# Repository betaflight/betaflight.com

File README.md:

## Project Description

This platform serves as a central hub for everything related to Betaflight, a popular open-source flight controller software used in FPV (First Person View) drones. This project provides users with documentation, development guidelines, downloads, build statistics, relations with sponsors, and blog updates. The website was built using [Docusaurus 2](https://docusaurus.io/), a modern static website generator. Our goal is to offer a user-friendly platform where users can easily access accurate and helpful resources, contributing to the overall improvement of the Betaflight community.

## Table of Contents

1. [Installation and Setup](#installation-and-setup)
2. [Usage Instructions](#usage-instructions)
3. [Troubleshooting](#troubleshooting)
4. [Build](#build)
5. [Deployment](#deployment)
6. [ESLint Prettier](#eslint-prettier)
7. [Contributing Guidelines](#contributing-guidelines)

## Installation and Setup

This project primarily consists of a documentation website built using Docusaurus. To run the project locally, follow these steps on a Linux machine:

Fork the repository. Then, clone the forked GitHub repository to your local machine:

```bash
git clone https://github.com/<yourusername>/betaflight.com.git
```

Navigate to the project directory:

```bash
cd betaflight.com
```

Install dependencies using npm:

```bash
npm i
```

If npm is not installed and you are using Linux, you can typically install npm using your distribution's package manager. For example, on Debian or Ubuntu-based systems, you can use apt:

```bash
sudo apt update
sudo apt install npm
```

Copy the .env.example file to .env and configure it according to your setup.

```bash
cp .env.example .env
```

The default is for a standard development environment:

```bash
URL=http://localhost:3000
BASE_PATH=/
ORG=betaflight
```

## Start the Local Development server

```bash
npm start
```

This command starts a local development server and opens up a browser window at http://localhost:3000. Most changes are reflected live without having to restart the server.

## Usage Instructions

Once Betaflight is set up, you can access the website locally through your browser. Users can easily navigate through the various sections of the platform to find the information they need. The Wiki section provides detailed documentation on Betaflight-related topics. The Development section is primarily for developers on how to contribute. The Downloads section offers access to essential resources such as Betaflight App, Firmware, Lua Tx Scripts, BlackBox Log Viewer, and more. Additionally, users can check Build Statistics, find Betaflight Sponsors, and stay up-to-date with the latest developments and announcements by checking the Blog section.

## Troubleshooting

If you encounter an issue while running npm start, especially related to syntax errors, it might be due to an incompatible version of Node.js. Follow these steps to resolve the issue:

Remove the current version of Node.js:

```bash
sudo apt remove nodejs
```

Install nvm (Node Version Manager) if you haven't already:

```bash
curl -o- https://raw.githubusercontent.com/nvm-sh/nvm/v0.39.1/install.sh | bash
```

Close and reopen your terminal to start using nvm, or run:

```bash
source ~/.bashrc
```

Install the latest LTS version of Node.js:

```bash
nvm install --lts
```

Activate the LTS version:

```bash
nvm use --lts
```

Try starting the application again by running:

```bash
npm run
```

## Build

To build the website for deployment, use the following command:

```bash
npm run build
```

This command generates static content into the `build` directory and can be served using any static contents hosting service.

## Deployment

Using SSH:

```bash
USE_SSH=true npm run deploy
```

Not using SSH:

```bash
GIT_USER=<Your GitHub username> npm run deploy
```

If you are using GitHub pages for hosting, this command is a convenient way to build the website and push to the `gh-pages` branch.

## ESLint Prettier

We use eslint and prettier for code formatting.

Husky is configured as a pre-commit hook to run both on commit, make sure it is setup correct and it runns before you commit your code.

## Contributing Guidelines

Please refer to the [CONTRIBUTING.md](./CONTRIBUTION.md) file for detailed guidelines on how to contribute to Betaflight.

Contributors agree to the [Contributor Licence Agreement](./CLA.md) when they open a pull request. See [LICENSE.md](./LICENSE.md) for the licence of the site and its content.

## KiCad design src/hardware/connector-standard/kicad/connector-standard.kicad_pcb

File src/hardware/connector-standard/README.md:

# Connector Standard Render Source

The KiCad project in `kicad/` is the source for the connector-standard schematic and PCB images published from `static/img/connector_standard/`.

## Crop Areas

Each connector must have the same lowercase, hyphenated crop name in both editors, for example `esc-connector`.

In the Schematic Editor:

1. Draw one rectangular rule area around the connector.
2. Leave all rule-area attributes disabled.
3. Group the rule area with the connector circuit.
4. Give the group the crop name.

In the PCB Editor:

1. Draw one rectangular rule area around the board coupon.
2. Allow tracks, vias, pads, copper pours, and footprints, and disable placement rules.
3. Give the rule area the same crop name as the schematic group.

The renderer validates that crop areas are axis-aligned rectangles, names are unique, and the two editors contain the same names. Hyphens in crop names become underscores in generated filenames.

Schematic crop guides are removed from a temporary project copy before export. PCB rule areas do not appear in the 3D renderer. The checked-in KiCad project is never modified by the script.

The PCB render uses the solder-mask colors from **Board Setup → Board Stackup → Physical Stackup**. Set both mask layers to black there to match the current connector-standard artwork.

## Commands

Install Node.js 20 or later and KiCad 10.0.0, then run:

```sh
npm ci
npm run validate:connector-standard
npm run render:connector-standard
```

`render:connector-standard` locates `kicad-cli` on `PATH` and in the standard KiCad 10 Windows installation directory. Set `KICAD_CLI` to use another executable:

```sh
KICAD_CLI=/opt/kicad/bin/kicad-cli npm run render:connector-standard
```

Generated files retain the existing documentation filenames:

```text
static/img/connector_standard/esc_connector_schematic.png
static/img/connector_standard/esc_connector_render.png
static/img/connector_standard/uart_connector_schematic.png
static/img/connector_standard/uart_connector_render.png
static/img/connector_standard/bf_connector_standard.svg
static/img/connector_standard/bf_connector_standard.pdf
```

CI runs `npm run check:connector-standard`, which renders into a temporary directory and fails when the generated artwork differs from its committed counterpart. PNG and SVG comparisons allow only a tightly bounded one-level antialiasing difference between platforms. The PDF embeds a deterministic SHA-256 source fingerprint and is checked by that fingerprint and its stable document structure because KiCad orders visually equivalent PDF drawing streams differently on Windows and Linux.

The repository-owned `render-theme.json` controls schematic colors, default PCB materials, lighting background, and other presentation details. Explicit board-stackup colors take precedence over its material defaults. KiCad is given an isolated temporary configuration directory, so rendering does not modify or depend on the user's KiCad preferences.

Geist Bold and Geist Mono Medium 1.7.2 are vendored in `fonts/` under the SIL Open Font License. The renderer exposes only this repository-owned font directory to KiCad, uses Geist Mono Medium for the schematic SVG and cropped schematic images, and uses Geist Bold for PCB silkscreen text. The downloadable schematic PDF retains KiCad's built-in stroke font because KiCad writes outline-font PDF subsets in nondeterministic order.

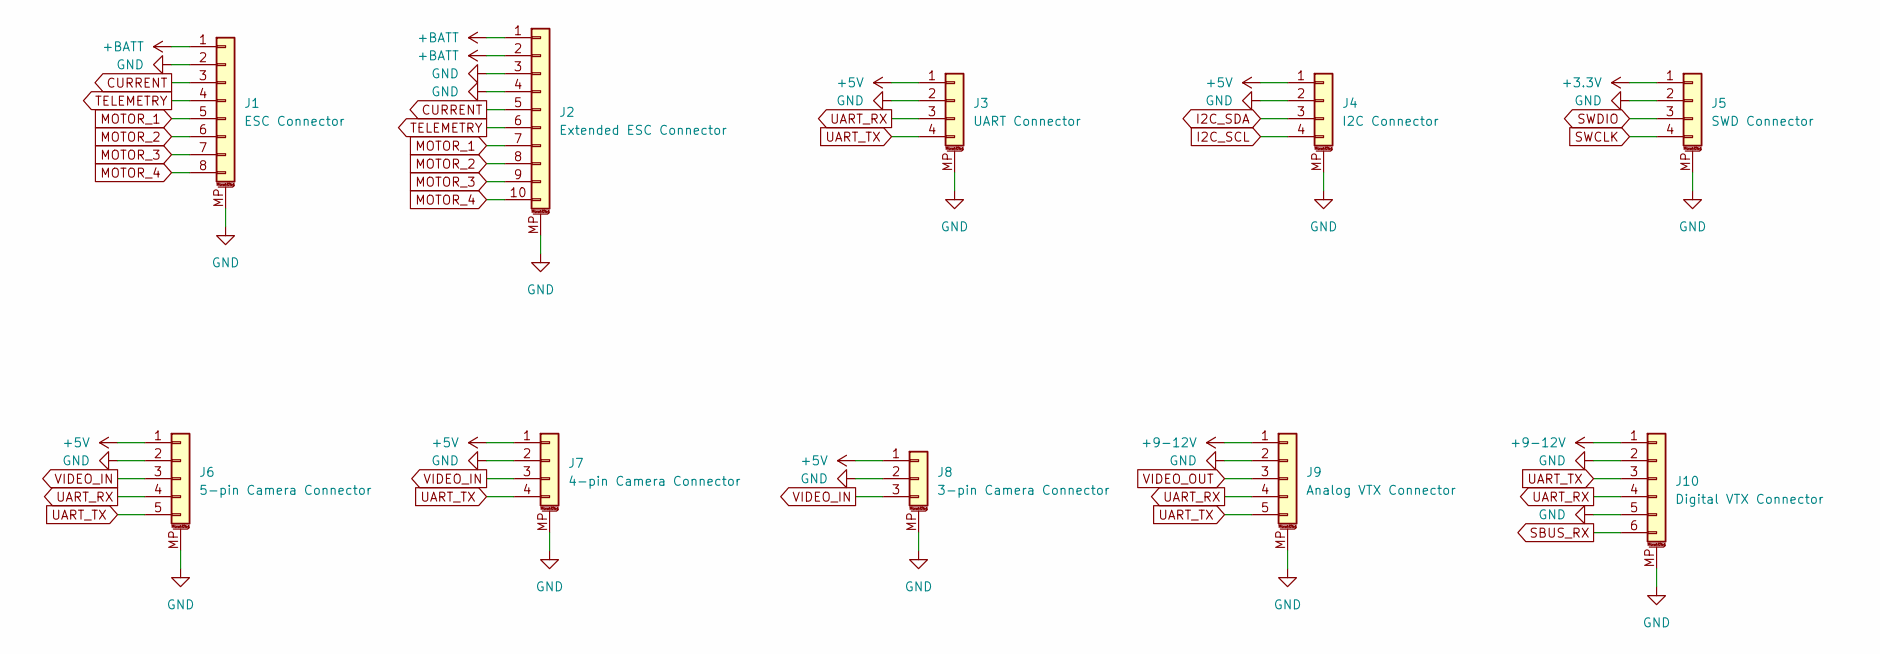
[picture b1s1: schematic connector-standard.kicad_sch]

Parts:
J1: ESC Connector; JST_SH_SM08B-SRSS-TB_1x08-1MP_P1.00mm_Horizontal
J2: Extended ESC Connector; JST_SH_SM10B-SRSS-TB_1x10-1MP_P1.00mm_Horizontal
J3: UART Connector; JST_SH_SM04B-SRSS-TB_1x04-1MP_P1.00mm_Horizontal
J4: I2C Connector; JST_SH_SM04B-SRSS-TB_1x04-1MP_P1.00mm_Horizontal
J5: SWD Connector; JST_SH_SM04B-SRSS-TB_1x04-1MP_P1.00mm_Horizontal
J6: 5-pin Camera Connector; JST_SH_SM05B-SRSS-TB_1x05-1MP_P1.00mm_Horizontal
J7: 4-pin Camera Connector; JST_SH_SM04B-SRSS-TB_1x04-1MP_P1.00mm_Horizontal
J8: 3-pin Camera Connector; JST_SH_SM03B-SRSS-TB_1x03-1MP_P1.00mm_Horizontal
J9: Analog VTX Connector; JST_SH_SM05B-SRSS-TB_1x05-1MP_P1.00mm_Horizontal
J10: Digital VTX Connector; JST_SH_SM06B-SRSS-TB_1x06-1MP_P1.00mm_Horizontal

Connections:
+3.3V: J5.1
+5V: J3.1, J4.1, J6.1, J7.1, J8.1
+9-12V: J9.1, J10.1
+BATT: J1.1, J2.1, J2.2
CURRENT: J1.3, J2.5
GND: J1.2, J1.MP (MountPin), J2.3, J2.4, J2.MP (MountPin), J3.2, J3.MP (MountPin), J4.2, J4.MP (MountPin), J5.2, J5.MP (MountPin), J6.2, J6.MP (MountPin), J7.2, J7.MP (MountPin), J8.2, J8.MP (MountPin), J9.2, J9.MP (MountPin), J10.2, J10.5, J10.MP (MountPin)
I2C_SCL: J4.4
I2C_SDA: J4.3
MOTOR_1: J1.5, J2.7
MOTOR_2: J1.6, J2.8
MOTOR_3: J1.7, J2.9
MOTOR_4: J1.8, J2.10
SBUS_RX: J10.6
SWCLK: J5.4
SWDIO: J5.3
TELEMETRY: J1.4, J2.6
UART_RX: J3.3, J6.4, J9.4, J10.4
UART_TX: J3.4, J6.5, J7.4, J9.5, J10.3
VIDEO_IN: J6.3, J7.3, J8.3
VIDEO_OUT: J9.3

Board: 2 copper layers, 10 parts (0 on the bottom side), 13 nets, no tracks yet.

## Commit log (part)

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2026-06-26 Sync 2026.6 notes with latest firmware and app master
    Firmware: add Xcore32m7 platform and ESP32-C5/P4 skeletons; correct the
    MAVLink caveat for landed mission transfer and GCS message-rate control;
    document Biquad-to-SVF filter and thrust_linearization rescale; altitude-hold
    rework, heading-gated poshold and poshold_without_mag removal; flag the
    IIM-42652 +/-2000 DPS re-tune as breaking, plus position-estimator, OSD
    local-time and dshot bitbang fixes.
2026-06-26 Add 2026.6 developer note on vendor MCU SDK submodule move
    Document the lib/main to lib/modules move for vendor MCU/SDK sources
    (APM32F4, GD32H7, STM32C5/H5/N6, X32M7, ESP-IDF, pico-sdk, libcanard),
    the recursive submodule refresh contributors need, and the new
    check-stale-submodule-paths CI guard.
2026-06-26 Add Betaflight 2026.6 release notes (#670)
    * Add Betaflight 2026.6 release notes
    Combined firmware and app release notes covering autopilot/flight plans
    (experimental, SITL only), ESP32/STM32H5/N6 platform support, battery
    profiles, optical flow position hold, Vue 3 app migration, and more.
    Bump sidebar positions on existing release notes to accommodate.
    * Fix hyphenation and spelling consistency in 2026.6 release notes
2026-06-30 docs: clarify GPS Rescue recovery stick inputs
    Clarify that recovery after an RC link loss requires either roll or
    pitch input beyond the configured failsafe stick threshold. Yaw input
    is ignored while GPS Rescue is active.
2026-06-30 docs: clarify GPS Rescue recovery stick inputs (#711)
    Clarify that recovery after an RC link loss requires either roll or
    pitch input beyond the configured failsafe stick threshold. Yaw input
    is ignored while GPS Rescue is active.
2026-06-30 Update ELRS SPI section in RN 2026.6 (#712)
    Update ELRS notes in RN 2026.6

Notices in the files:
README.md:
License: All rights reserved
